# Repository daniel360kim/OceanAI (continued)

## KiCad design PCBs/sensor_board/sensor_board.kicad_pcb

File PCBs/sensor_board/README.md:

# Transmitter Board

## This directory contains the PCB designs for the sensor board.
### The front of the submarine contains several sensors underwater: a pressure transducer and a thermistor. The pressure transducer is used to measure the pressure of the water. The thermistor is used to measure the temperature of the water. The sensor board reads these sensors and sends the data to the main board through I2C. 
### Power:
* 3.3V (no voltage regulator onboard - must be clean 3.3V)
### Sensors:
* Analog input for external pressure transducer
* 10K Thermistor for water temperature readings
### Communication:
* Communicated to the submarine [main_board](https://github.com/daniel360kim/OceanAI/tree/master/main_board) through I2C.
* The board features SWD interface for debugging and is programmed through SWD.

## What's done?
* Schematic is finished.
* PCB layout is finished
* 3D models and fabrication outputs are generated
## What's to do?
* Ordering and fabrication

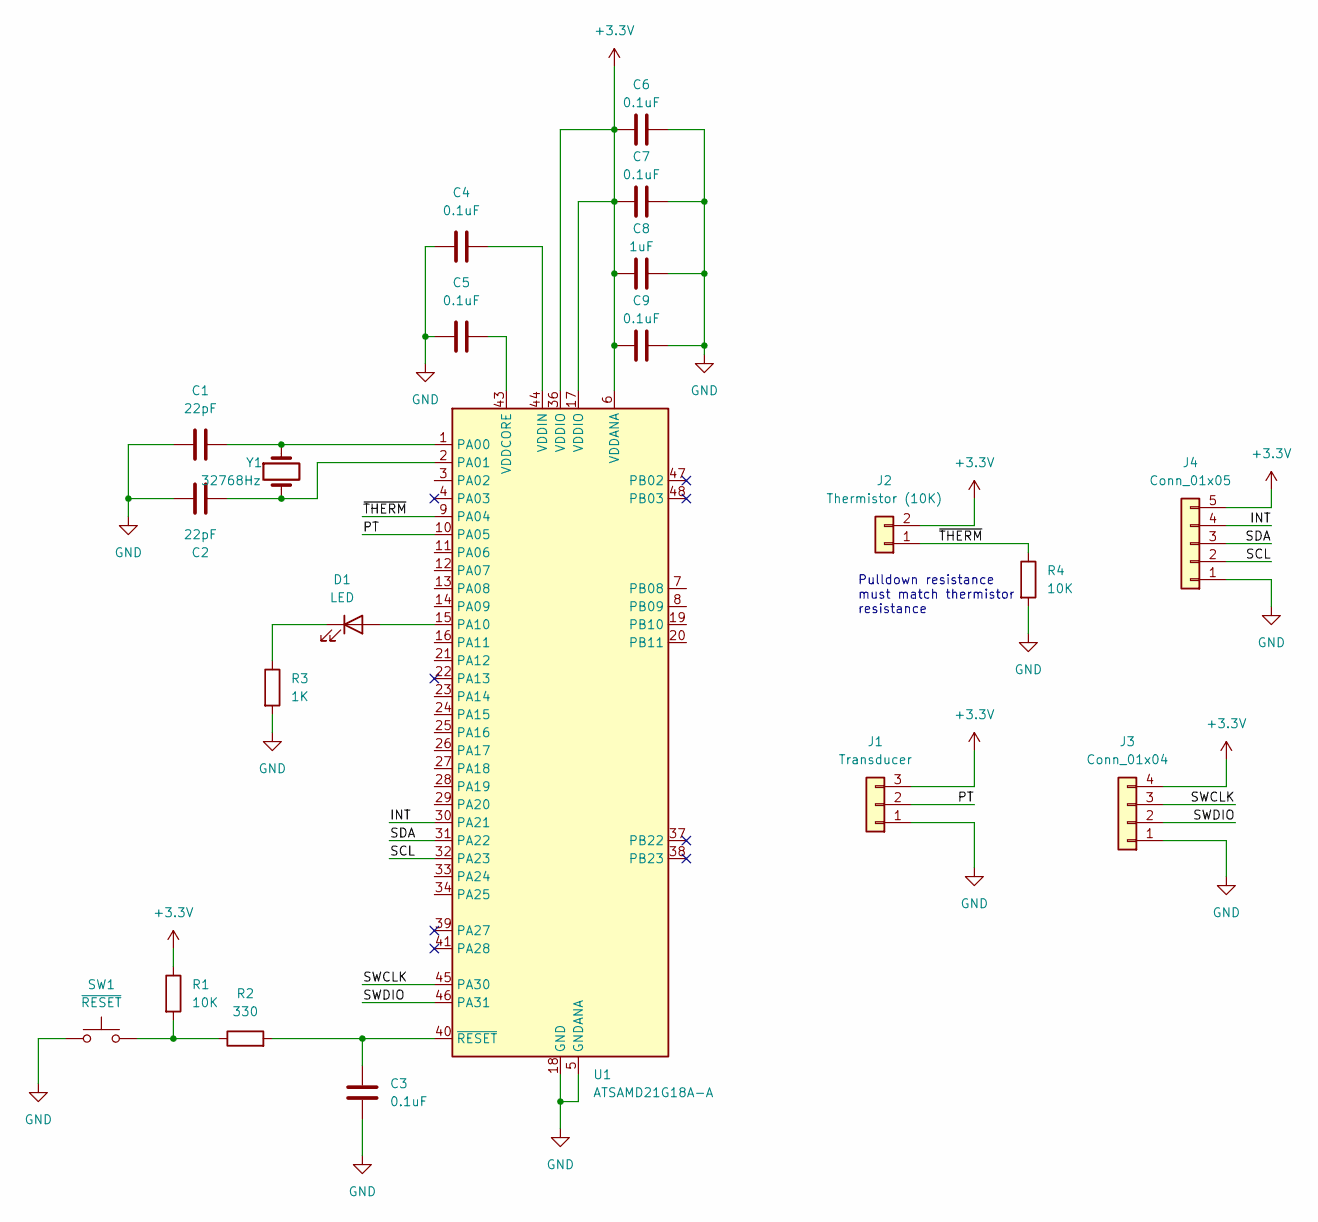
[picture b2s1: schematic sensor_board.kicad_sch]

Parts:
C1, C2: 22pF; C_0603_1608Metric
C3, C4, C5, C6, C7, C9: 0.1uF; C_0603_1608Metric
C8: 1uF; C_0603_1608Metric
D1: LED; LED_0603_1608Metric
J1: Transducer; PinHeader_1x03_P2.54mm_Vertical
J2: Thermistor (10K); PinHeader_1x02_P2.54mm_Vertical
J3: Conn_01x04; PinHeader_1x04_P2.54mm_Vertical
J4: Conn_01x05; PinHeader_1x05_P2.54mm_Vertical
R1, R4: 10K; R_0603_1608Metric
R2: 330; R_0603_1608Metric
R3: 1K; R_0603_1608Metric
SW1: ~{RESET}; PTS810SJG250SMTRLFS
U1: ATSAMD21G18A-A; TQFP-48_7x7mm_P0.5mm
Y1: 32768Hz; XTAL_ABS07-32.768KHZ-T

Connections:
+3V3: C6.1, C7.1, C8.1, C9.1, J1.3, J2.2, J3.4, J4.5, R1.1, U1.6 (VDDANA), U1.17 (VDDIO), U1.36 (VDDIO)
/INT: J4.4, U1.30 (PA21)
/PT: J1.2, U1.10 (PA05)
/SCL: J4.2, U1.32 (PA23)
/SDA: J4.3, U1.31 (PA22)
/SWCLK: J3.3, U1.45 (PA30)
/SWDIO: J3.2, U1.46 (PA31)
/~THERM: J2.1, R4.1, U1.9 (PA04)
GND: C1.1, C2.1, C3.2, C4.1, C5.1, C6.2, C7.2, C8.2, C9.2, J1.1, J3.1, J4.1, R3.2, R4.2, SW1.1, SW1.2, U1.5 (GNDANA), U1.18 (GND), U1.35 (GND), U1.42 (GND)
unnamed: C1.2, U1.1 (PA00), Y1.1
unnamed: C2.2, U1.2 (PA01), Y1.2
unnamed: C3.1, R2.2, U1.40 (~RESET)
unnamed: C4.2, U1.44 (VDDIN)
unnamed: C5.2, U1.43 (VDDCORE)
unnamed: D1.1 (K), R3.1
unnamed: D1.2 (A), U1.15 (PA10)
unnamed: R1.2, R2.1, SW1.3, SW1.4

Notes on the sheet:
Pulldown resistance must match thermistor resistance

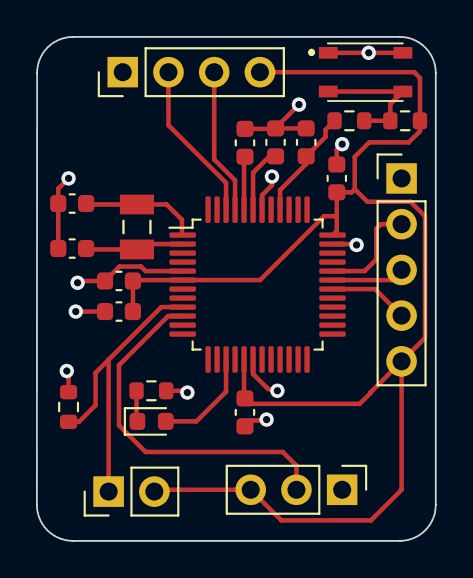
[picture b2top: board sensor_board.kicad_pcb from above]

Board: 2 copper layers, 22.2 x 28.0 mm, 21 parts (0 on the bottom side), 17 nets.

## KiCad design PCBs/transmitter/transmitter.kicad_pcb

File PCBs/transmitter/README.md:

# Transmitter Board

## This directory contains the PCB designs for the transmitter board.
### Since RF and GPS do not function well underwater, the submarine will feature an optional transmitter module that is floating in the water. The transmitter board is a simple, inexpensive, and easy to use module that can be used to transmit data to the submarine. Powered by the ATSAMD21G18A, the board has several features:
### Power:
* 1S LiPo battery 
* Solar power to recharge LiPo battery
### Sensors:
* BMP388 pressure sensor
* 10K Thermistor for water temperature readings
### Communication:
* Communicated to the submarine [main_board](https://github.com/daniel360kim/OceanAI/tree/master/main_board) through an ethernet cable through I2C.
* I2C optimized for long range communication using the LTC4311 chip.
* The board has 2 SPI interfaces: One for a 2.4GHz RF module and one for a LoRa radio module.
* The board has a UART interface for GPS connectivity.
* The board features SWD interface for debugging. 

## What's done?
* Schematic is finished.
* PCB layout is finished
* 3D models and fabrication outputs are generated
## What's to do?
* Ordering and fabrication

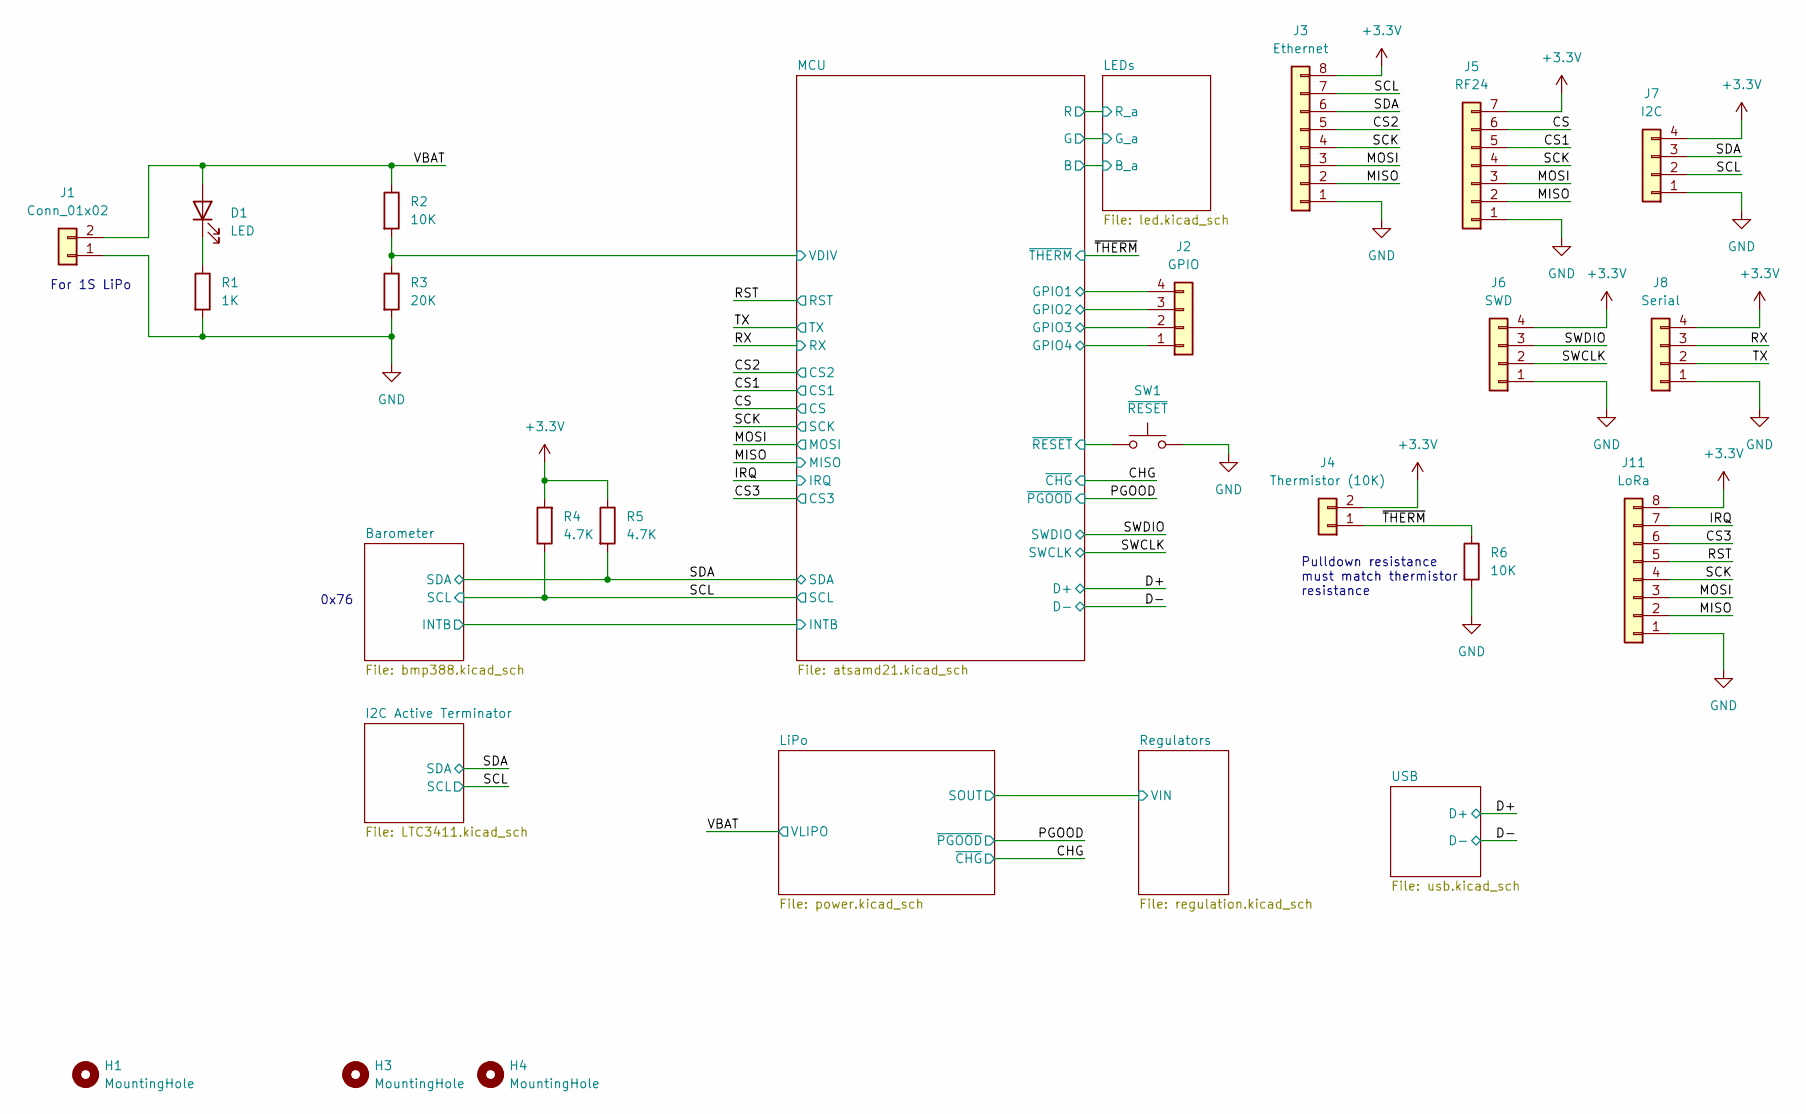
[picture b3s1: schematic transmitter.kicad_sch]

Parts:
D1: LED; LED_0603_1608Metric
H1, H3, H4: MountingHole; MountingHole_2mm
J1: Conn_01x02; JST_EH_B2B-EH-A_1x02_P2.50mm_Vertical
J2: GPIO; PinHeader_1x04_P2.54mm_Vertical
J3: Ethernet; PinHeader_1x08_P2.54mm_Vertical
J4: Thermistor (10K); PinHeader_1x02_P2.54mm_Vertical
J5: RF24; PinHeader_1x07_P2.54mm_Vertical
J6: SWD; PinHeader_1x04_P2.54mm_Vertical
J7: I2C; PinHeader_1x04_P2.54mm_Vertical
J8: Serial; PinHeader_1x04_P2.54mm_Vertical
J11: LoRa; PinHeader_1x08_P2.54mm_Vertical
R1: 1K; R_0603_1608Metric
R2, R6: 10K; R_0603_1608Metric
R3: 20K; R_0603_1608Metric
R4, R5: 4.7K; R_0603_1608Metric
SW1: ~{RESET}; PTS810SJG250SMTRLFS

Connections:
+3V3: J3.8, J4.2, J5.7, J6.4, J7.4, J8.4, J11.8, R4.2, R5.1; also elsewhere on the board
/CS: J5.6; also elsewhere on the board
/CS1: J5.5; also elsewhere on the board
/CS2: J3.5; also elsewhere on the board
/CS3: J11.6; also elsewhere on the board
/IRQ: J11.7; also elsewhere on the board
/MCU/GPIO1: J2.4; also elsewhere on the board
/MCU/GPIO2: J2.3; also elsewhere on the board
/MCU/GPIO3: J2.2; also elsewhere on the board
/MCU/GPIO4: J2.1; also elsewhere on the board
/MCU/VDIV: R2.2, R3.1; also elsewhere on the board
/MCU/~RESET: SW1.1, SW1.2; also elsewhere on the board
/MISO: J3.2, J5.2, J11.2; also elsewhere on the board
/MOSI: J3.3, J5.3, J11.3; also elsewhere on the board
/RST: J11.5; also elsewhere on the board
/RX: J8.3; also elsewhere on the board
/SCK: J3.4, J5.4, J11.4; also elsewhere on the board
/SCL: J3.7, J7.2, R4.1; also elsewhere on the board
/SDA: J3.6, J7.3, R5.2; also elsewhere on the board
/SWCLK: J6.2; also elsewhere on the board
/SWDIO: J6.3; also elsewhere on the board
/TX: J8.2; also elsewhere on the board
/VBAT: D1.2 (A), J1.2, R2.1; also elsewhere on the board
/~THERM: J4.1, R6.1; also elsewhere on the board
GND: J1.1, J3.1, J5.1, J6.1, J7.1, J8.1, J11.1, R1.2, R3.2, R6.2, SW1.3, SW1.4; also elsewhere on the board
unnamed: D1.1 (K), R1.1

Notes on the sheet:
For 1S LiPo
Pulldown resistance must match thermistor resistance
0x76

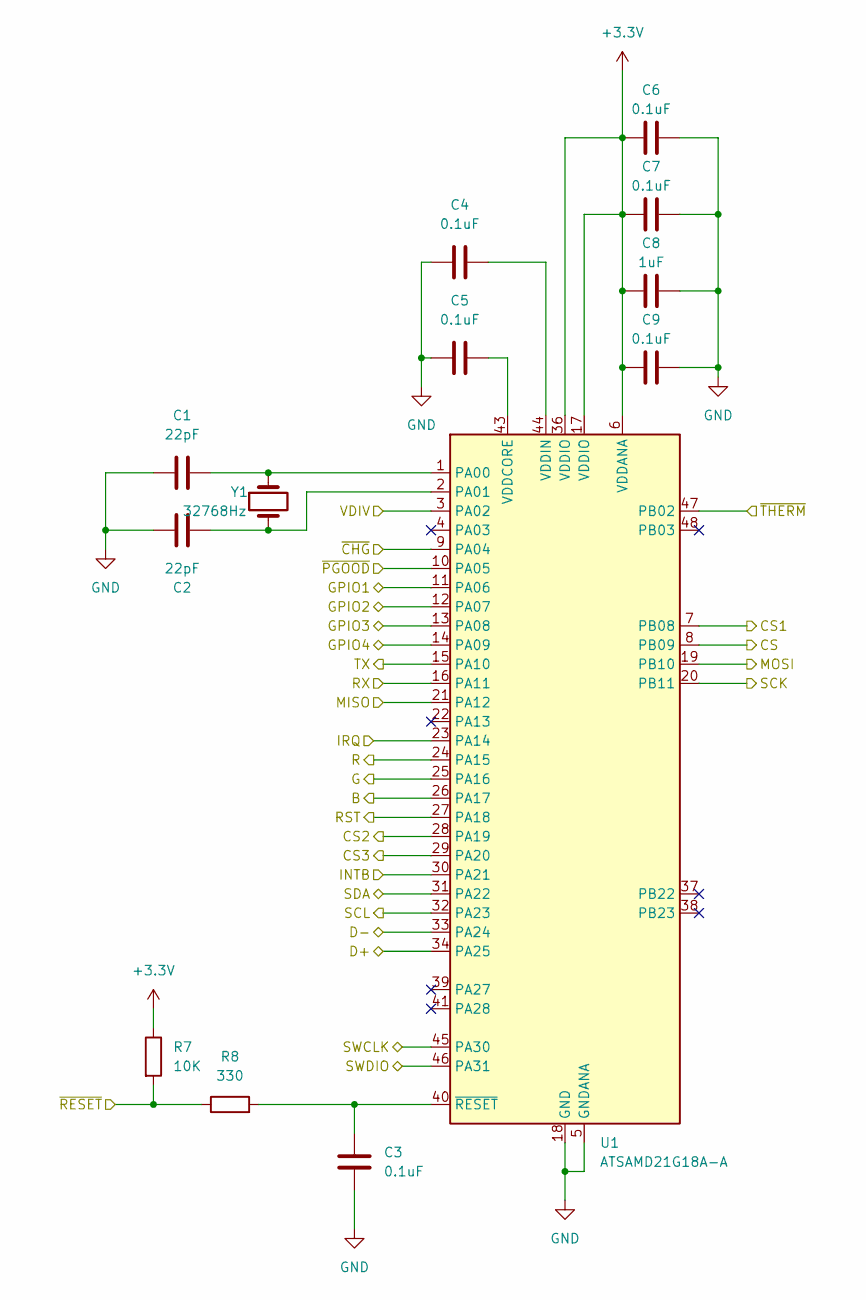
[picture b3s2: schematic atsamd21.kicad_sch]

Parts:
C1, C2: 22pF; C_0603_1608Metric
C3, C4, C5, C6, C7, C9: 0.1uF; C_0603_1608Metric
C8: 1uF; C_0603_1608Metric
R7: 10K; R_0603_1608Metric
R8: 330; R_0603_1608Metric
U1: ATSAMD21G18A-A; TQFP-48_7x7mm_P0.5mm
Y1: 32768Hz; XTAL_ABS07-32.768KHZ-T

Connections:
+3V3: C6.1, C7.1, C8.1, C9.1, R7.1, U1.6 (VDDANA), U1.17 (VDDIO), U1.36 (VDDIO); also elsewhere on the board
/Barometer/INTB: U1.30 (PA21); also elsewhere on the board
/CHG: U1.9 (PA04); also elsewhere on the board
/CS: U1.8 (PB09); also elsewhere on the board
/CS1: U1.7 (PB08); also elsewhere on the board
/CS2: U1.28 (PA19); also elsewhere on the board
/CS3: U1.29 (PA20); also elsewhere on the board
/D+: U1.34 (PA25); also elsewhere on the board
/D-: U1.33 (PA24); also elsewhere on the board
/IRQ: U1.23 (PA14); also elsewhere on the board
/LEDs/B_a: U1.26 (PA17); also elsewhere on the board
/LEDs/G_a: U1.25 (PA16); also elsewhere on the board
/LEDs/R_a: U1.24 (PA15); also elsewhere on the board
/MCU/GPIO1: U1.11 (PA06); also elsewhere on the board
/MCU/GPIO2: U1.12 (PA07); also elsewhere on the board
/MCU/GPIO3: U1.13 (PA08); also elsewhere on the board
/MCU/GPIO4: U1.14 (PA09); also elsewhere on the board
/MCU/VDIV: U1.3 (PA02); also elsewhere on the board
/MCU/~RESET: R7.2, R8.1; also elsewhere on the board
/MISO: U1.21 (PA12); also elsewhere on the board
/MOSI: U1.19 (PB10); also elsewhere on the board
/PGOOD: U1.10 (PA05); also elsewhere on the board
/RST: U1.27 (PA18); also elsewhere on the board
/RX: U1.16 (PA11); also elsewhere on the board
/SCK: U1.20 (PB11); also elsewhere on the board
/SCL: U1.32 (PA23); also elsewhere on the board
/SDA: U1.31 (PA22); also elsewhere on the board
/SWCLK: U1.45 (PA30); also elsewhere on the board
/SWDIO: U1.46 (PA31); also elsewhere on the board
/TX: U1.15 (PA10); also elsewhere on the board
/~THERM: U1.47 (PB02); also elsewhere on the board
GND: C1.1, C2.1, C3.2, C4.1, C5.1, C6.2, C7.2, C8.2, C9.2, U1.5 (GNDANA), U1.18 (GND), U1.35 (GND), U1.42 (GND); also elsewhere on the board
unnamed: C1.2, U1.1 (PA00), Y1.1
unnamed: C2.2, U1.2 (PA01), Y1.2
unnamed: C3.1, R8.2, U1.40 (~RESET)
unnamed: C4.2, U1.44 (VDDIN)
unnamed: C5.2, U1.43 (VDDCORE)

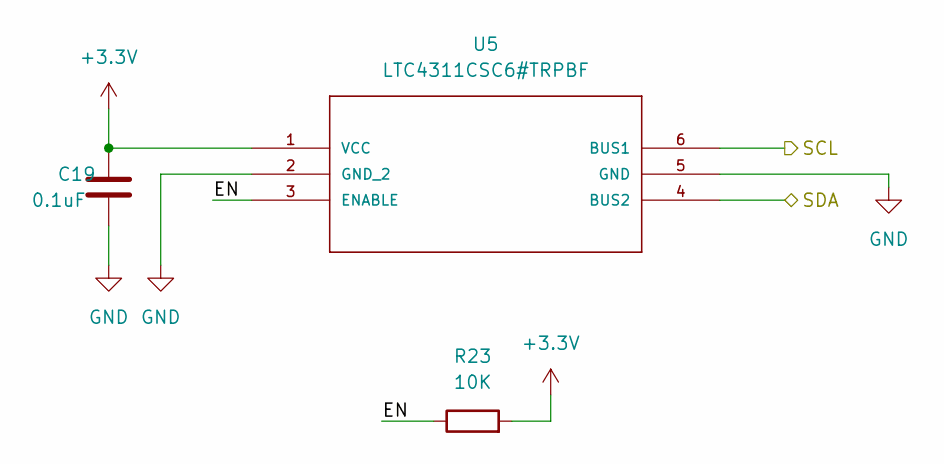
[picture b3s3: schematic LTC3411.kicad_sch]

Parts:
C19: 0.1uF; C_0603_1608Metric
R23: 10K; R_0603_1608Metric
U5: LTC4311CSC6#TRPBF; LTC4311CSC6_TRPBF; MANUFACTURER_PART_NUMBER ltc4311csc6#pbf

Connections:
+3V3: C19.1, R23.2, U5.1 (VCC); also elsewhere on the board
/I2C Active Terminator/EN: R23.1, U5.3 (ENABLE)
/SCL: U5.6 (BUS1); also elsewhere on the board
/SDA: U5.4 (BUS2); also elsewhere on the board
GND: C19.2, U5.2 (GND_2), U5.5 (GND); also elsewhere on the board

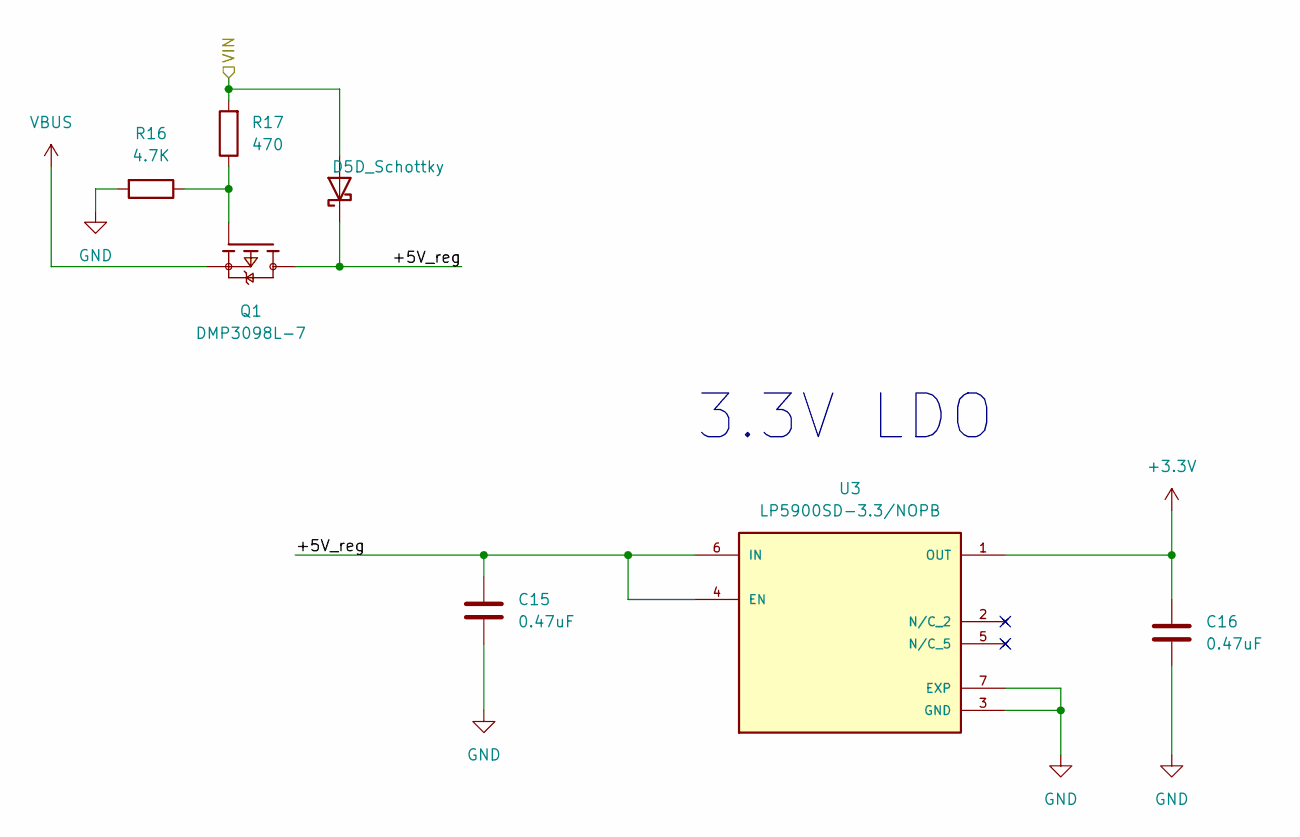
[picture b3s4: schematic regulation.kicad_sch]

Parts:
C15, C16: 0.47uF; C_0603_1608Metric
D5: D_Schottky; 1N4148
Q1: DMP3098L-7; DMP3098L; PARTREV 8 - 2
R16: 4.7K; R_0603_1608Metric
R17: 470; R_0603_1608Metric
U3: LP5900SD-3.3/NOPB; LP5900SD-3.3_NOPB; PARTREV R

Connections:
+3V3: C16.1, U3.1 (OUT); also elsewhere on the board
/LiPo/SOUT: D5.A, R17.2; also elsewhere on the board
/Regulators/+5V_reg: C15.1, D5.C (K), Q1.3, U3.4 (EN), U3.6 (IN)
GND: C15.2, C16.2, R16.2, U3.3 (GND), U3.7 (EXP); also elsewhere on the board
unnamed: Q1.1, R16.1, R17.1
VBUS: Q1.2; also elsewhere on the board

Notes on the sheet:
3.3V LDO

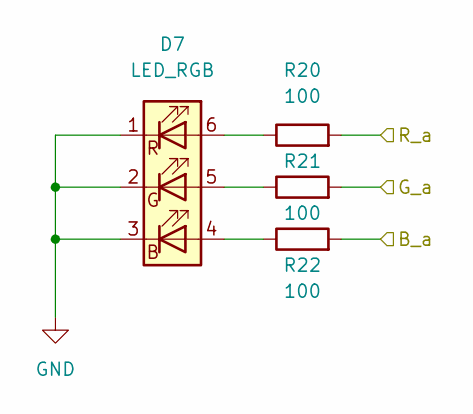
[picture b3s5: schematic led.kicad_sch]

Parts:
D7: LED_RGB; LED_RGB_5050-6
R20, R21, R22: 100; R_0603_1608Metric

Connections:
/LEDs/B_a: R22.2; also elsewhere on the board
/LEDs/G_a: R21.2; also elsewhere on the board
/LEDs/R_a: R20.2; also elsewhere on the board
GND: D7.1 (RK), D7.2 (GK), D7.3 (BK); also elsewhere on the board
unnamed: D7.4 (BA), R22.1
unnamed: D7.5 (GA), R21.1
unnamed: D7.6 (RA), R20.1

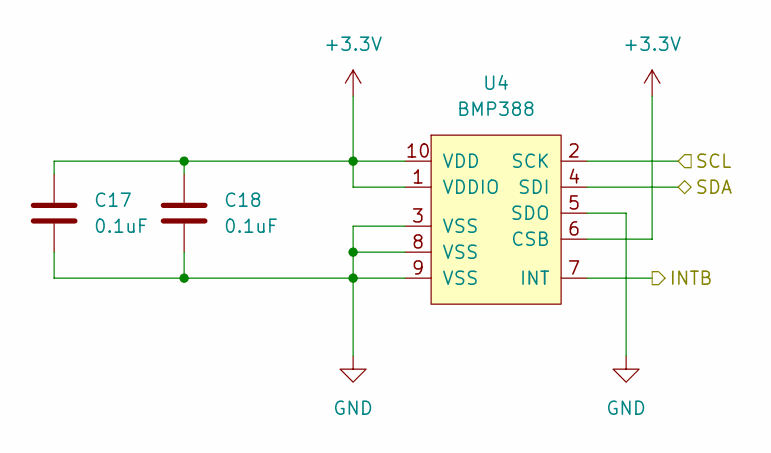
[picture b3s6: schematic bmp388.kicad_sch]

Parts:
C17, C18: 0.1uF; C_0603_1608Metric
U4: BMP388; bmp388

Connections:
+3V3: C17.1, C18.1, U4.1 (VDDIO), U4.6 (CSB), U4.10 (VDD); also elsewhere on the board
/Barometer/INTB: U4.7 (INT); also elsewhere on the board
/SCL: U4.2 (SCK); also elsewhere on the board
/SDA: U4.4 (SDI); also elsewhere on the board
GND: C17.2, C18.2, U4.3 (VSS), U4.5 (SDO), U4.8 (VSS), U4.9 (VSS); also elsewhere on the board

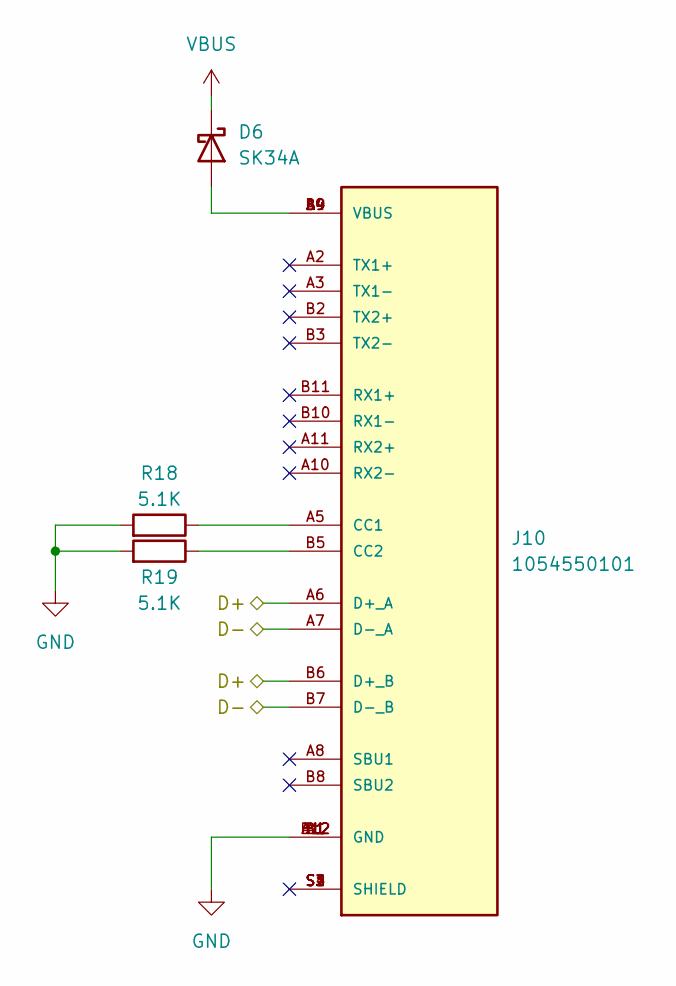
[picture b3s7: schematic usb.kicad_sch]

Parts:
D6: SK34A; D_SMA
J10: 1054550101; MOLEX_1054550101; PARTREV A2
R18, R19: 5.1K; R_0603_1608Metric

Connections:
/D+: J10.A6 (D+_A), J10.B6 (D+_B); also elsewhere on the board
/D-: J10.A7 (D-_A), J10.B7 (D-_B); also elsewhere on the board
GND: J10.A1 (GND), J10.A12 (GND), J10.B1 (GND), J10.B12 (GND), R18.2, R19.2; also elsewhere on the board
unnamed: D6.2 (A), J10.A4 (VBUS), J10.A9 (VBUS), J10.B4 (VBUS), J10.B9 (VBUS)
unnamed: J10.A5 (CC1), R18.1
unnamed: J10.B5 (CC2), R19.1
VBUS: D6.1 (K); also elsewhere on the board

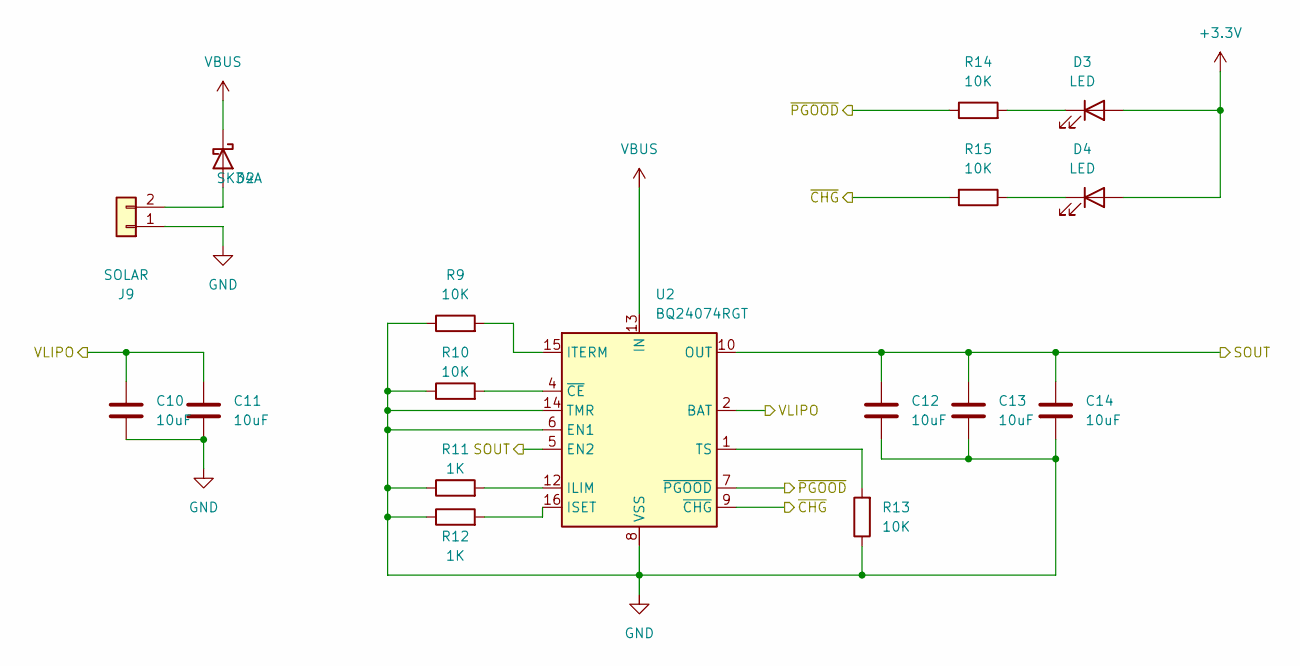
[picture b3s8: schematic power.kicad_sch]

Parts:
C10, C11, C12, C13, C14: 10uF; C_0603_1608Metric
D2: SK34A; D_SMA
D3, D4: LED; LED_0603_1608Metric
J9: SOLAR; JST_EH_B2B-EH-A_1x02_P2.50mm_Vertical
R9, R10, R13, R14, R15: 10K; R_0603_1608Metric
R11, R12: 1K; R_0603_1608Metric
U2: BQ24074RGT; VQFN-16-1EP_3x3mm_P0.5mm_EP1.6x1.6mm

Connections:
+3V3: D3.2 (A), D4.2 (A); also elsewhere on the board
/CHG: R15.2, U2.9 (~CHG); also elsewhere on the board
/LiPo/SOUT: C12.1, C13.1, C14.1, U2.5 (EN2), U2.10 (OUT), U2.11 (OUT); also elsewhere on the board
/PGOOD: R14.1, U2.7 (~PGOOD); also elsewhere on the board
/VBAT: C10.1, C11.1, U2.2 (BAT), U2.3 (BAT); also elsewhere on the board
GND: C10.2, C11.2, C12.2, C13.2, C14.2, J9.1, R9.1, R10.1, R11.1, R12.1, R13.1, U2.6 (EN1), U2.8 (VSS), U2.14 (TMR), U2.17 (VSS); also elsewhere on the board
unnamed: D2.2 (A), J9.2
unnamed: D3.1 (K), R14.2
unnamed: D4.1 (K), R15.1
unnamed: R9.2, U2.15 (ITERM)
unnamed: R10.2, U2.4 (~CE)
unnamed: R11.2, U2.12 (ILIM)
unnamed: R12.2, U2.16 (ISET)
unnamed: R13.2, U2.1 (TS)
VBUS: D2.1 (K), U2.13 (IN); also elsewhere on the board

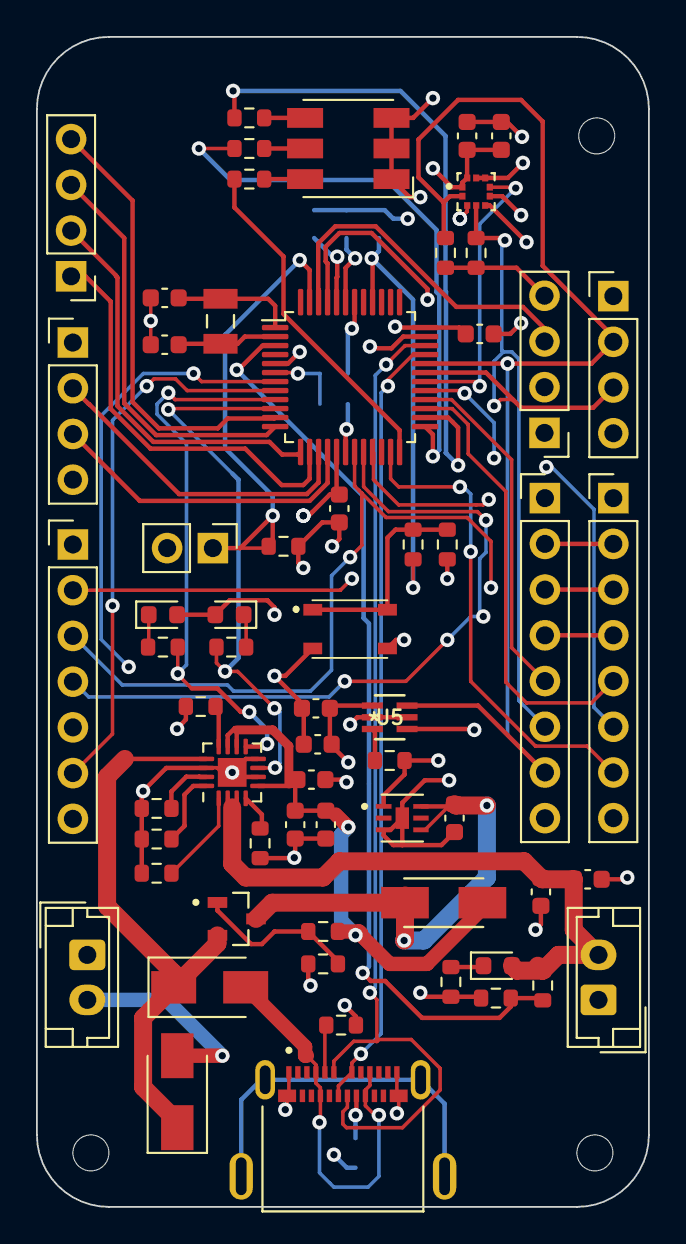
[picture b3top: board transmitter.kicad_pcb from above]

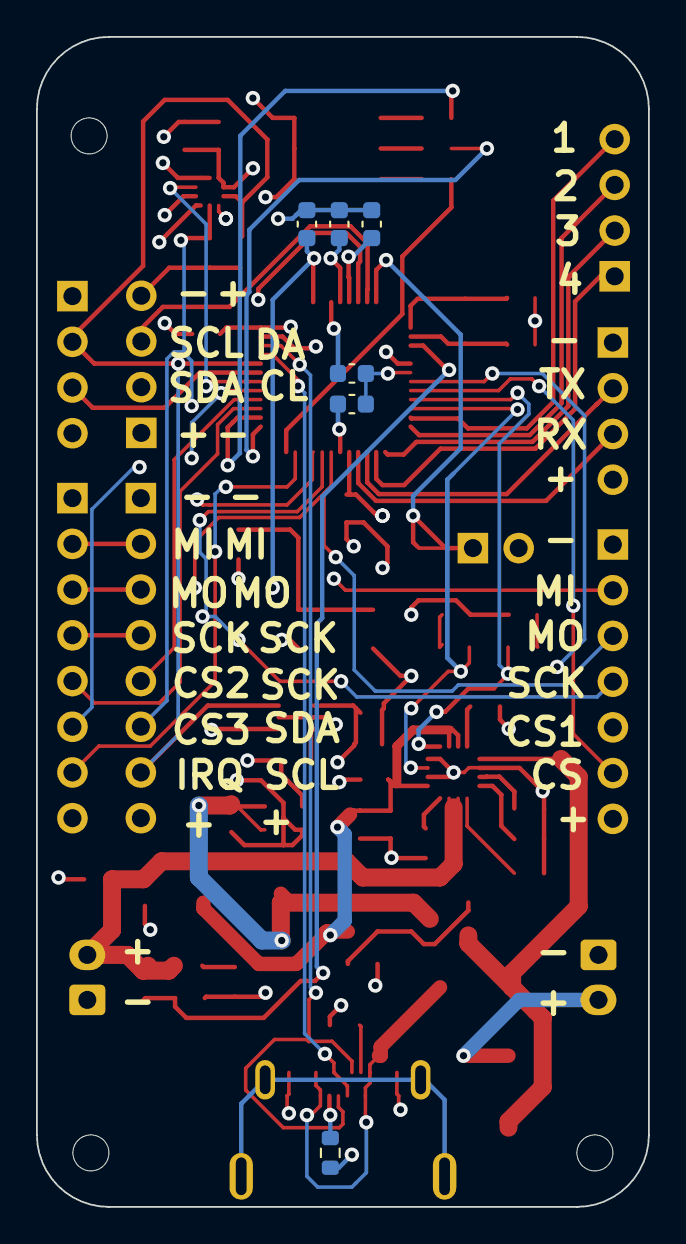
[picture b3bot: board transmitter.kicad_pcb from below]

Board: 4 copper layers, 34.0 x 65.0 mm, 71 parts (6 on the bottom side), 58 nets.

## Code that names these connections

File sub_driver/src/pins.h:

/**
 * @file pins.h
 * @author Daniel Kim
 * @brief Pin definitions for the main board
 * @version 1
 * @date 2022-06-12
 * 
 * @copyright Copyright (c) 2022 OceanAI (https://github.com/daniel360kim/OceanAI)
 * 
 */

/************************************************************************************
 * Teensy 4.1 (IMXRT1062) Pin Assignments on OceanAI main board
 * https://www.pjrc.com/teensy/teensyduino.html
************************************************************************************/
#ifndef pins_h
#define pins_h

#include <Arduino.h>

///// Stepper Motors /////
//Buoyancy Engine
constexpr uint8_t RST_b = 21;
constexpr uint8_t DIR_b = 24;
constexpr uint8_t STP_b = 25;
constexpr uint8_t SLP_b = 26;

constexpr uint8_t MS1_b = 9;
constexpr uint8_t MS2_b = 7;
constexpr uint8_t MS3_b = 8;

//Pitexprch Manipulation Engine
constexpr uint8_t RST_p = 40;
constexpr uint8_t DIR_p = 38;
constexpr uint8_t STP_p = 39;
constexpr uint8_t SLP_p = 41;

constexpr uint8_t MS1_p = 28;
constexpr uint8_t MS2_p = 29;
constexpr uint8_t MS3_p = 30;

/////expr Limit Switches /////
constexpr uint8_t STOP_b = 32; //buoyancy engine limit switch
constexpr uint8_t STOP_p = 31; //pitch manipulation limit switch

/////expr Sensor (I2C) Interrupts (Data-ready only)
constexpr uint8_t ACC_int = 34; //BMI088 Accelerometer
constexpr uint8_t GYR_int = 33; //BMI088 Gyroscope
constexpr uint8_t BAR_int = 35; //BMP388 Barometer
constexpr uint8_t MAG_int = 36; //LIS3MDLTR Magnetometer 

/////expr Indication /////
//RGBexpr A
constexpr uint8_t RED_a = 0;
constexpr uint8_t GRN_a = 1;
constexpr uint8_t BLU_a = 2;

//RGBexpr B
constexpr uint8_t RED_b = 22;
constexpr uint8_t GRN_b = 23;
constexpr uint8_t BLU_b = 15;

//Sigexprnal
constexpr uint8_t SIGNAL = 5;

//Buzexprzer
constexpr uint8_t BUZZ = 14;

/////expr Voltage Reading /////
constexpr uint8_t v_div = 16;

/////expr Total Dissolved Sensor ADC /////
constexpr uint8_t TDS = 17;

/////expr Comms /////
//RFexpr
constexpr uint8_t RX_RF = 3;
constexpr uint8_t TX_RF = 4;
constexpr uint8_t SET = 6;

//GPSexpr
constexpr uint8_t RX_GPS = 21;
constexpr uint8_t TX_GPS = 20;

/////expr SPI /////
constexpr uint8_t CS_VD = 10;
constexpr uint8_t CS = 37;

#endif

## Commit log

2022-07-13 init commit
2022-07-14 Added compiled executable
2022-07-14 created README
2022-07-14 created logs
2022-07-14 deleted README
2022-07-14 deleted unneeded vector
2022-07-14 removed vscode
2022-07-14 modified .gitignore
2022-07-14 modified: .gitignore
2022-07-14 modified gitignore
2022-07-14 modified README
2022-07-14 modified LICENSE
2022-07-14 SD logging and rewind
2022-07-14 Updated OS
2022-07-14 Created README for sub_driver
2022-07-14 Optimized OV2640 camera operation
2022-07-17 added receiver_driver
2022-07-17 fixed gitignore
2022-07-17 organized directories
2022-07-17 added documentation for receiver_driver
2022-07-17 Added directory guide
2022-07-18 fixed interval issues
2022-07-23 start information logging
2022-07-25 made matrix class
2022-07-25 reordered directories
2022-07-25 fixed "include"
2022-07-25 created stepper motor driver
2022-07-27 finished board schematic
2022-07-27 created PCB readme
2022-07-27 updated directory guide
2022-07-27 updated schematics
2022-07-27 updated gitignore
2022-07-28 completed PCB layout
2022-07-28 created fabrication outputs
2022-07-28 deleted videos
2022-07-29 created sensor board
2022-07-29 created media
2022-07-29 specified programmer
2022-07-29 edited delimeters
2022-08-12 created sensor_board configs
2022-08-12 i2c send data impl
2022-08-13 external sensor support
2022-08-13 scraper
2022-08-14 communication with sensor board
2022-08-15 converted from struct send to byte send
2022-08-15 updated to <cmath>
2022-08-17 removed unneeded functions
2022-08-17 static circular buffer
2022-08-20 completed stepper driver
2022-08-22 created derived class
2022-09-02 stepper
2022-09-10 updated glider model
2022-09-11 switched to static queue instead of dynamic
2022-09-11 changed sensor class to singleton
2022-09-11 updated to singleton structure
2022-09-13 stepper utility
2022-09-13 added barometer filtering
2022-09-14 Documented
2022-09-14 updated start condition logging
2022-09-24 switched to std::queue instead of CircularBuffer
2022-09-24 removed unused files
2022-09-24 updated buoyancy stepper
2022-09-24 fixed LED pin defs
2022-09-24 updated comms with buoy
2022-09-24 crash reporting
2022-09-25 updated sd interface
2022-09-25 created tensorflow micro test
2022-09-29 added sub pictures
2022-10-01 updated to nanosecond resolution timers
2022-10-01 fixed ns to sec conversion factors
2022-10-01 readded crash report
2022-10-01 edited startup sequence
2022-10-01 added PlatformDetection
2022-10-01 created state automation classes
2022-10-01 created states diagrams
2022-10-01 implemented finite state automation
2022-10-01 deleted vision
2022-10-02 created timer class
2022-10-02 added timed function implementation
2022-10-02 switched to dynamic queue
2022-10-02 sd logging feature additions
2022-10-02 added error checking
2022-10-03 fixed licensing
2022-10-22 updated debug
2022-10-23 optimization october!
2022-10-23 optimized SD translate
2022-10-23 updated sd logging
2022-10-28 Message Pack Implementation
2022-10-29 json logging
2022-10-29 update json parser
2022-10-29 removed sensor driver
2022-10-29 added json ending
2022-10-29 implemente json ending
2022-11-02 updated vision
2022-11-04 cleanup
2022-11-04 documentation
2022-11-04 added FASTRUN functionality
2022-11-04 updated dependency modifications
2022-11-05 updated json parser
2022-11-05 updated json parsing
2022-11-06 updated external sensor API
2022-11-06 removed unneeded dependencies
2022-11-13 updated env paths
2022-11-23 updated camera API
2022-11-24 removed deprecated tflite models
2022-11-24 added inferencing API
2022-11-25 added end hook
2022-11-25 updated json parse
2022-11-26 added telemetry functionality
2022-11-26 truncated telemetry packet
2022-11-26 removed pitch data transmission
2022-11-26 removed unneeded project
2022-11-26 created GUI project template
2022-11-27 updated GUI
2022-12-04 updated stepper functionality
2022-12-10 updated gui functionality
2022-12-10 added space filling
2022-12-14 updated to direct telemetry
2022-12-20 updated direct transport manager
2022-12-20 created project logo
2022-12-20 added build information
2022-12-22 updated data file name
2022-12-25 added compiler path download instructions
2022-12-25 changed data log struct nomenclature
2022-12-26 updated debug class
2022-12-27 added variadic arg functionality to debugger
2022-12-27 updated CPU log API
2022-12-29 created gitignore for PCB
2022-12-29 updated schematic 3d models
2022-12-29 made logged data more specific
2022-12-29 changed from singleton -> individual functions
2023-01-01 updated CAD model
2023-01-01 added renders
2023-01-01 removed unneeded model
2023-01-01 removed unneeded return
2023-01-01 added GUI configurations
2023-01-01 changed transport monitor interval to 5Hz
2023-01-01 added return type to barometer initialization
2023-01-01 added UI and Debug output collision warning
2023-01-02 removed mission duration object
2023-01-02 updated build directions
2023-01-03 updated 3d model directories
2023-01-03 removed unneeded includes
2023-01-03 updated from stdint -> cstdint
2023-01-03 removed FASTRUN functionality
2023-01-03 removed disfunctional back to top button
2023-01-03 removed unneeded auto generated readmes
2023-01-07 added run2 mosaics
2023-01-20 updated 3D board models
2023-01-20 added new images
2023-01-20 created hardware in the loop class
2023-01-21 created data extractor
2023-01-21 added 3d models
2023-02-04 updated nomenclature of schematic
2023-02-15 updated schematic labels
2023-02-15 added large file system
2023-02-15 removed deprecated renders
2023-02-15 removed unneeded data files
2023-02-15 updated json parser example data
2023-02-15 removed error manager class
2023-02-15 added HITL data
2023-02-15 updated icons
2023-02-15 updated project configurations
2023-02-15 added HITL functionality to GUI
2023-02-15 updated hitl functionality on auv
2023-02-18 removed unneeded images
2023-02-25 updated main board layers
2023-03-10 added numeric outputs to navigation page
2023-03-10 updated camera features
2023-04-03 updated file symbols
2023-04-03 removed unneeded states
2023-04-03 removed angle wrapping. 0-360 -> -180-180
2023-04-03 allow for multiple voltage readings
2023-04-03 fixed pin nomenclature
2023-04-03 removed unneeded diving state
2023-04-03 fixed led test code
2023-04-04 more documentation and cleanup
2023-04-05 removed deprecated directories
2023-04-05 adjusted ballast endpoint setpoint
2023-04-05 added training code
2023-04-05 added inferencing code
2023-04-05 removed auto generated file
2023-04-05 changed status of learning model
2023-04-05 added instructions for ml model inferencing
2023-04-05 added automatic pitch control
2023-04-05 cleaned up HITL logging
2023-04-05 made stepper controls more concise
2023-04-06 added pitch control mechanism
2023-04-06 added AUV 3d model for GUI
2023-04-06 added pitch control within the pitch class
2023-04-08 removed unneeded model indexes
2023-04-08 added precompilation conditions for HITL data
2023-04-23 updated ECAD settings
2023-04-23 updated fbx models for GUI
2023-04-23 changed positions for automated pitch control
2023-07-19 updated video link
